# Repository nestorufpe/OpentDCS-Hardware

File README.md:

# OpentDCS_Wifi_Shield
The schematics for the OpentDCS wifi shield

All design files made with KiCad PCB design software.
http://kicad-pcb.org/

Disclaimer:

These files are presented AS IS, with no representation of warranty or functionality.
Designs are subject to chage without notice.

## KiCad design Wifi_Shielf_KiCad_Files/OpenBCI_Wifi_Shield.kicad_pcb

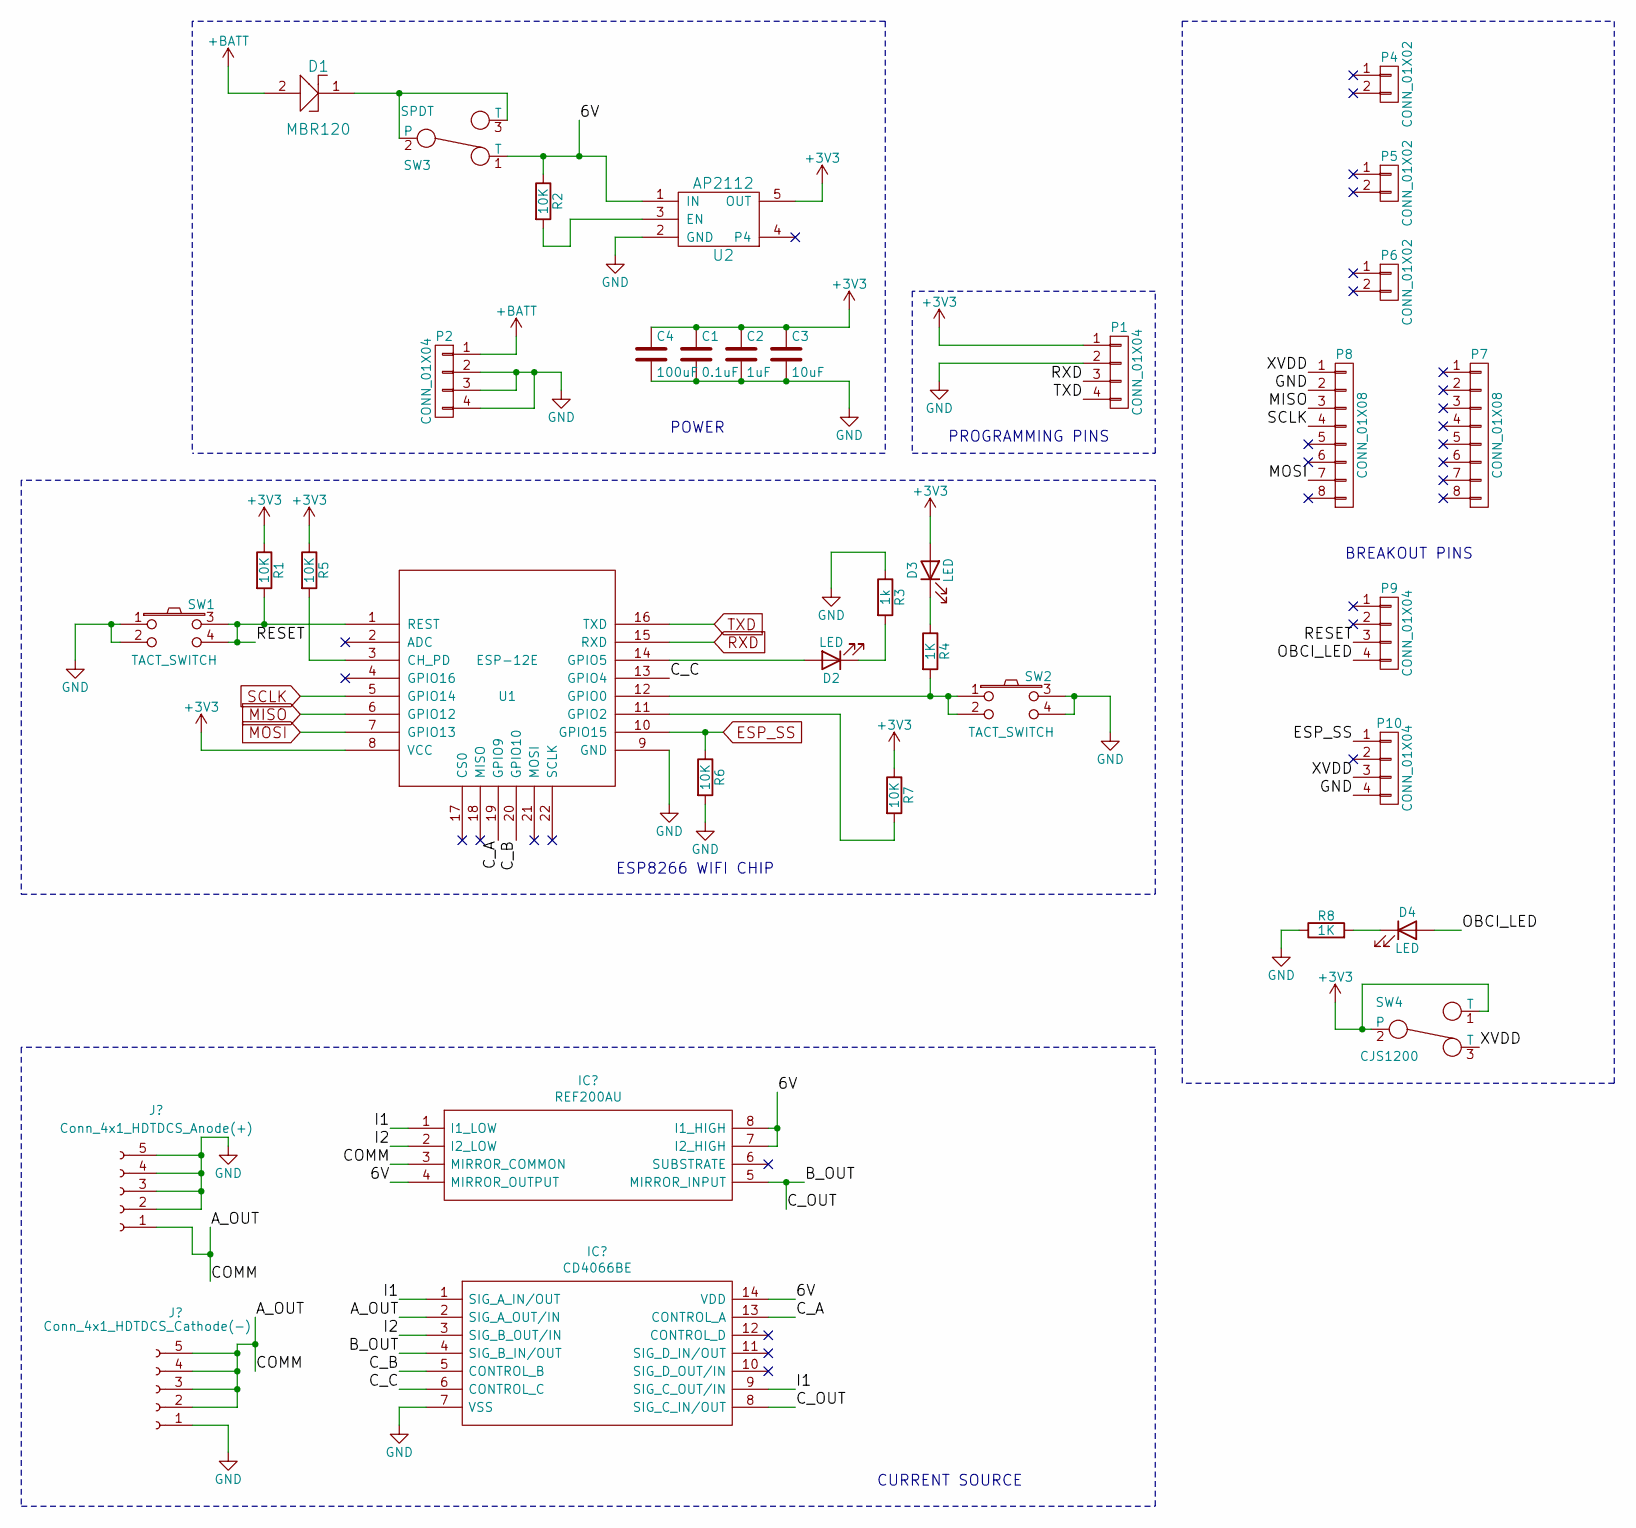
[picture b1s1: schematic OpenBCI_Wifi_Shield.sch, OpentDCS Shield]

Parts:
C1: 0.1uF; C_0603
C2: 1uF; C_0603
C3: 10uF; C_0603
C4: 100uF; C_1210
D1: MBR120; SOD-123FL
D2, D3, D4: LED; LED_0603
P1, P9, P10: CONN_01X04; Socket_Strip_Straight_1x04
P2: CONN_01X04; JST_RA_SMT
P4, P5, P6: CONN_01X02; Socket_Strip_Straight_1x02
P7, P8: CONN_01X08; Socket_Strip_Straight_1x08
R1, R2, R5, R6, R7: 10K; C_0603
R3: 1k; C_0603
R4, R8: 1K; C_0603
SW1, SW2: TACT_SWITCH; PTS810
SW3: SPDT; PCM12SMTR
SW4: CJS1200; CJS-1200TA
U1: ESP-12E; ESP-12E-SMD
U2: AP2112; SOT-23-5

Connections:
+3V3: C1.1, C2.1, C3.1, C4.1, D3.2 (A), P1.1, R1.1, R5.1, R7.1, SW4.1 (T), SW4.2, U1.8 (VCC), U2.5 (OUT)
+BATT: D1.2, P2.1
/6V: R2.1, SW3.1 (T), U2.1 (IN); also elsewhere on the board
/C_A: U1.19 (GPIO9); also elsewhere on the board
/C_B: U1.20 (GPIO10); also elsewhere on the board
/C_C: U1.13 (GPIO4); also elsewhere on the board
/OBCI_LED: D4.2 (A), P9.4
/RESET: P9.3, R1.2, SW1.3, SW1.4, U1.1 (REST)
/XVDD: P8.1, P10.3, SW4.3 (T)
ESP_SS: P10.1, R6.1, U1.10 (GPIO15)
GND: C1.2, C2.2, C3.2, C4.2, P1.2, P2.2, P2.3, P2.4, P8.2, P10.4, R3.1, R6.2, R8.1, SW1.1, SW1.2, SW2.3, SW2.4, U1.9 (GND), U2.2 (GND); also elsewhere on the board
MISO: P8.3, U1.6 (GPIO12)
MOSI: P8.7, U1.7 (GPIO13)
unnamed: D1.1, SW3.2, SW3.3 (T)
unnamed: D2.1 (K), R3.2
unnamed: D2.2 (A), U1.14 (GPIO5)
unnamed: D3.1 (K), R4.1
unnamed: D4.1 (K), R8.2
unnamed: R2.2, U2.3 (EN)
unnamed: R4.2, SW2.1, SW2.2, U1.12 (GPIO0)
unnamed: R5.2, U1.3 (CH_PD)
unnamed: R7.2, U1.11 (GPIO2)
RXD: P1.3, U1.15 (RXD)
SCLK: P8.4, U1.5 (GPIO14)
TXD: P1.4, U1.16 (TXD)

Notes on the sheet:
BREAKOUT PINS
POWER
ESP8266 WIFI CHIP
PROGRAMMING PINS
CURRENT SOURCE

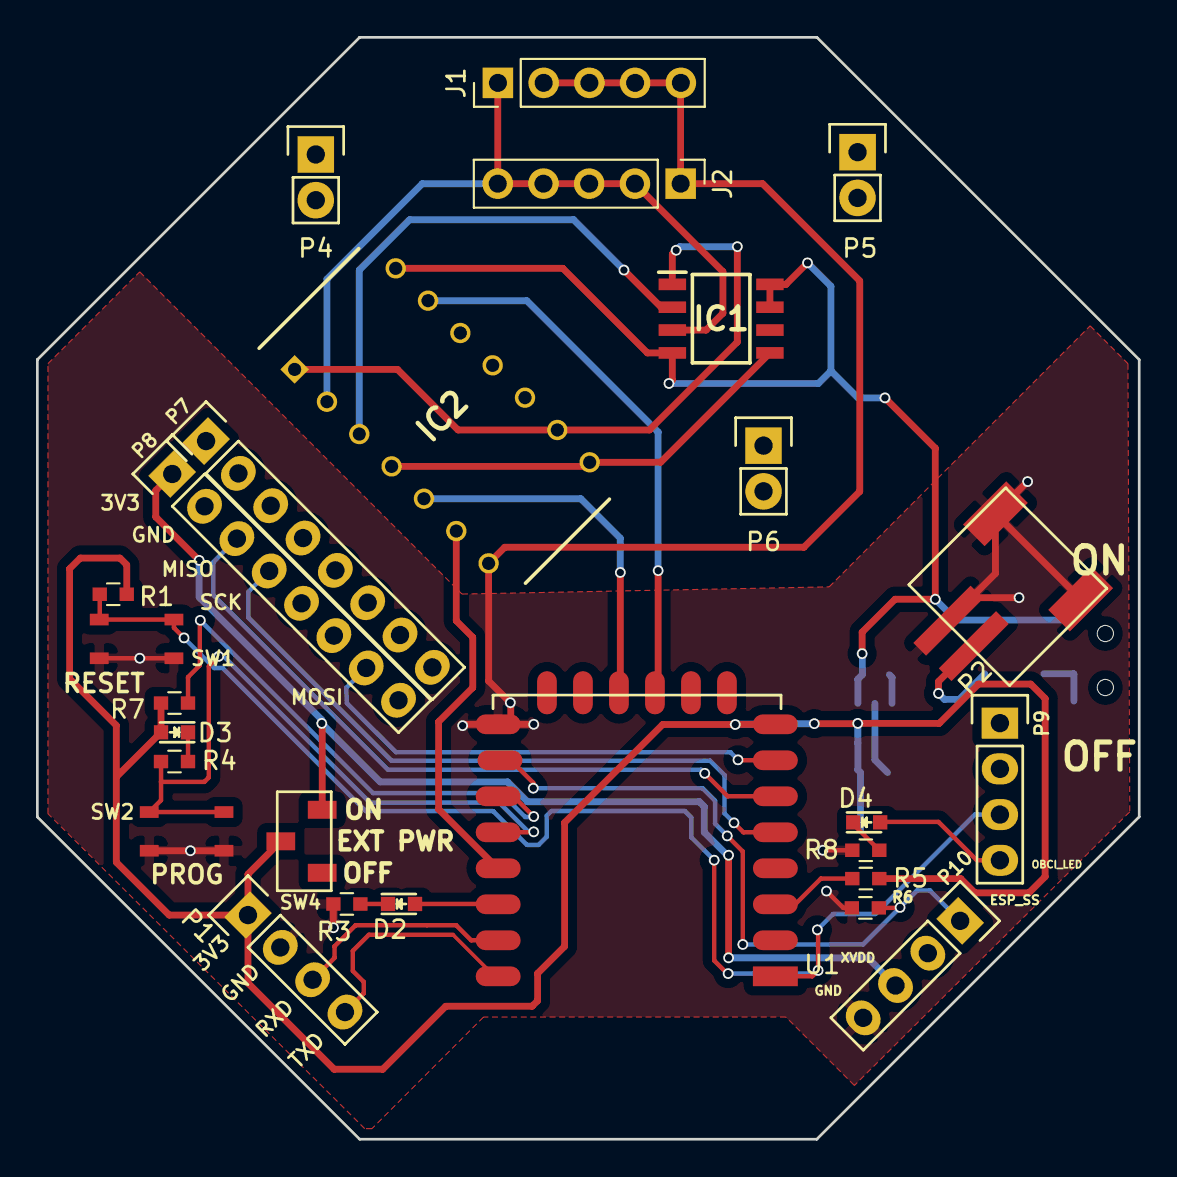
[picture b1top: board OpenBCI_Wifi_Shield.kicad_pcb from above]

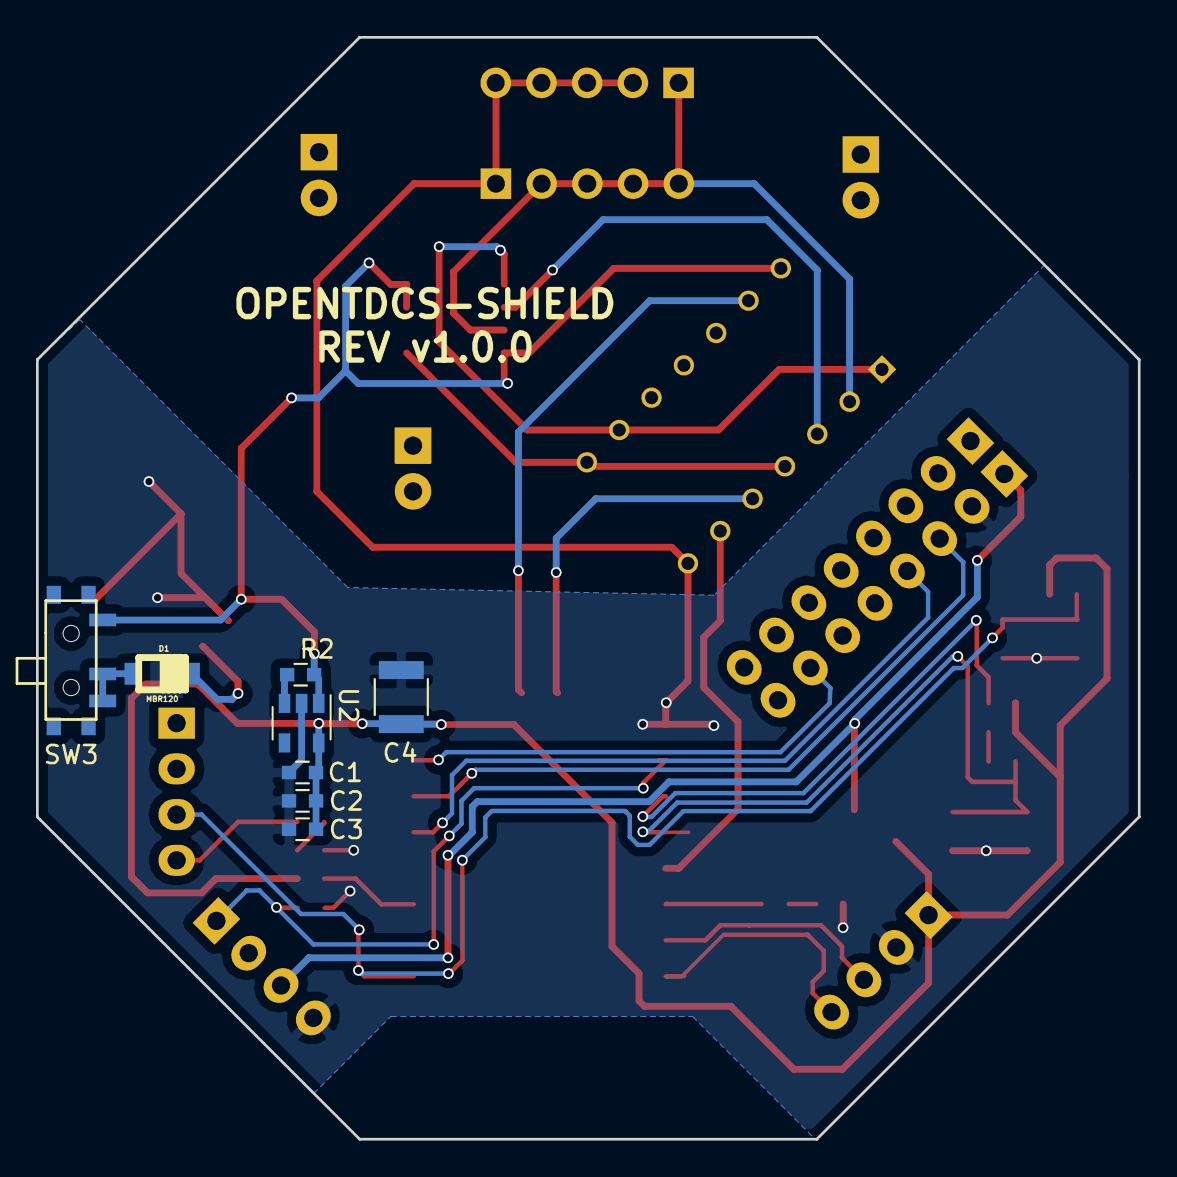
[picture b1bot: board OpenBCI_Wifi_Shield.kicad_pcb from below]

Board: 2 copper layers, 61.2 x 61.2 mm, 35 parts (8 on the bottom side), 29 nets.

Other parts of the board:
IC1: REF200AU; SOIC127P600X175-8N
IC2: CD4066BE; DIP794W53P254L1930H508Q14N
J1: Conn_4x1_HDTDCS_Anode(+); PinHeader_1x05_P2.54mm_Vertical
J2: Conn_4x1_HDTDCS_Cathode(-); PinHeader_1x05_P2.54mm_Vertical

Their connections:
/6V: IC1.4, IC1.7, IC1.8, IC2.14; also elsewhere on the board
/A_OUT: IC1.3, IC2.2, J1.1, J2.2, J2.3, J2.4, J2.5
/B_OUT: IC1.5, IC2.4, IC2.8
/C_A: IC2.13; also elsewhere on the board
/C_B: IC2.5; also elsewhere on the board
/C_C: IC2.6; also elsewhere on the board
/I1: IC1.1, IC2.1, IC2.9
/I2: IC1.2, IC2.3
GND: IC2.7, J1.2, J1.3, J1.4, J1.5, J2.1; also elsewhere on the board

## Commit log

2022-08-30 Fisrt commit
2022-09-05 Aproveitamento do ESP-12E
2022-09-06 Add dos conectores no esquemático de tdcs
2022-09-07 Adição dos gerber files e layout da pcb
2022-09-07 Atualiazação do layout (3.3v conectado)
2022-09-07 Adiciona os novos gerber files
